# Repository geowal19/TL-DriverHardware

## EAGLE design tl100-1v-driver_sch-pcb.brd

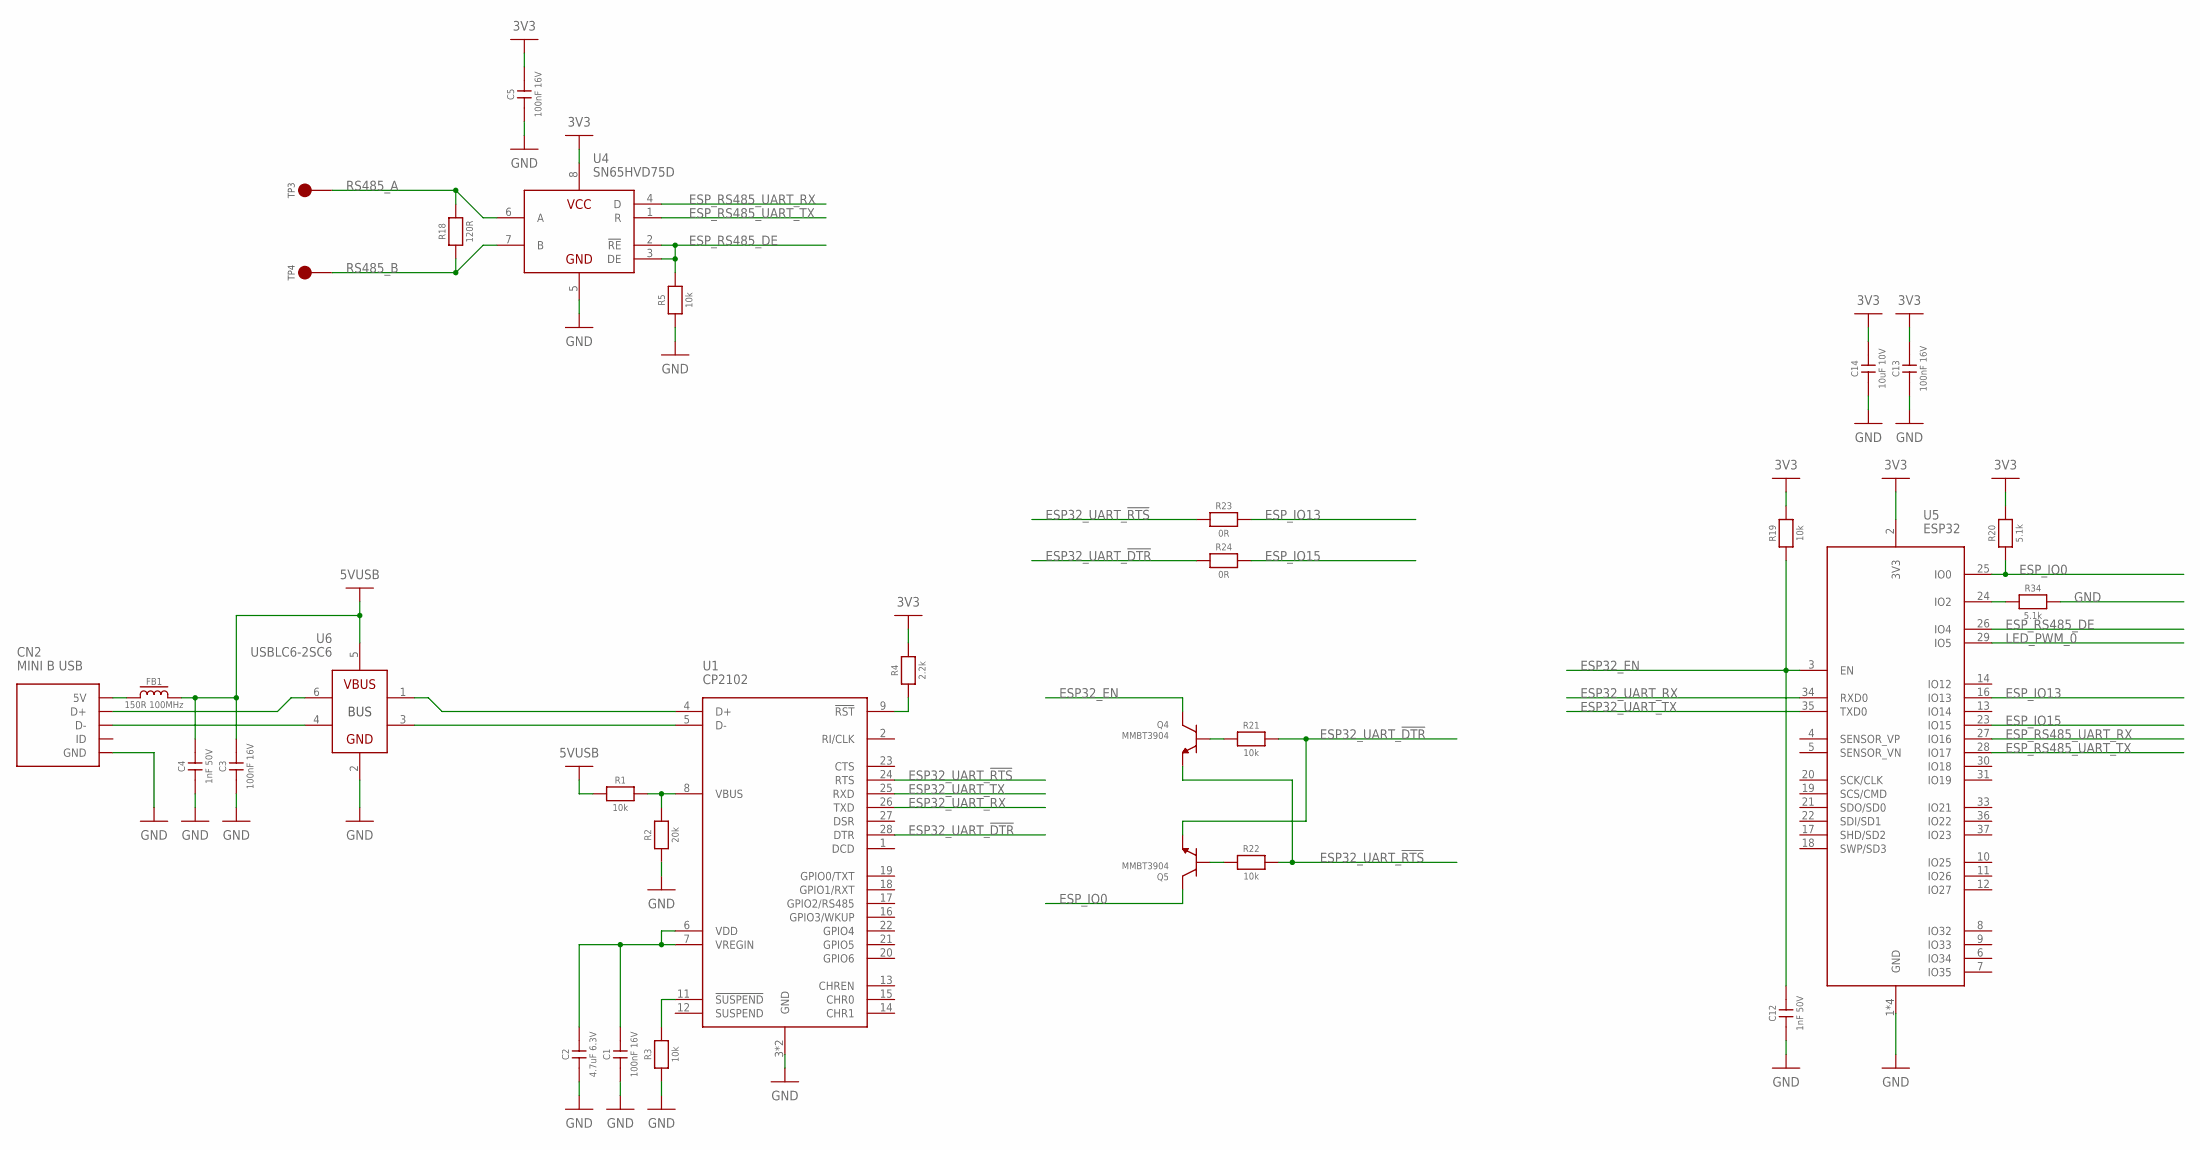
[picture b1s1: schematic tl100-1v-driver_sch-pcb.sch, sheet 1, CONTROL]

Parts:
C1, C3, C5, C13: 100nF 16V; 0603
C2: 4.7uF 6.3V; 0603
C4, C12: 1nF 50V; 0603
C14: 10uF 10V; 0603
CN2: MINI B USB; MUSB-05-S-B-SM-A
FB1: 150R 100MHz; 1206
Q4, Q5: MMBT3904; SOT23-3
R1, R3, R5, R19, R21, R22: 10k; 0603
R2: 20k; 0603
R4: 2.2k; 0603
R18: 120R; 0603
R20, R34: 5.1k; 0603
R23, R24: 0R; 0603
TP3, TP4: 2MM_TEST_POINT; 2MM_TEST_PAD
U1: CP2102; QFN28
U4: SN65HVD75D; SO8
U5: ESP32; ESP32-WROOM-32D
U6: USBLC6-2SC6; SOT23-6

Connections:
3V3: C5.2, C13.2, C14.2, R4.2, R19.2, R20.2, U4.8 (VCC), U5.2 (3V3); also elsewhere on the board
5VUSB: C3.2, C4.2, FB1.2, R1.1, U6.5 (VBUS); also elsewhere on the board
ESP32_EN: C12.2, Q4.2 (C), R19.1, U5.3 (EN)
ESP32_UART_!DTR: Q5.3 (E), R21.2, R24.1, U1.28 (DTR)
ESP32_UART_!RTS: Q4.3 (E), R22.2, R23.1, U1.24 (RTS)
ESP32_UART_RX: U1.26 (TXD), U5.34 (RXD0)
ESP32_UART_TX: U1.25 (RXD), U5.35 (TXD0)
ESP_IO0: Q5.2 (C), R20.1, U5.25 (IO0)
ESP_IO13: R23.2, U5.16 (IO13)
ESP_IO15: R24.2, U5.23 (IO15)
ESP_RS485_DE: R5.2, U4.2 (!RE), U4.3 (DE), U5.26 (IO4)
ESP_RS485_UART_RX: U4.4 (D), U5.27 (IO16)
ESP_RS485_UART_TX: U4.1 (R), U5.28 (IO17)
GND: C1.1, C2.1, C3.1, C4.1, C5.1, C12.1, C13.1, C14.1, CN2.GND, CN2.SHIELD1 (GND), CN2.SHIELD2 (GND), CN2.SHIELD3 (GND), CN2.SHIELD4 (GND), R2.1, R3.1, R5.1, R34.2, U1.3 (GND), U1.29 (GND), U4.5 (GND), U5.1 (GND), U5.15 (GND), U5.38 (GND), U5.39 (GND), U6.2 (GND); also elsewhere on the board
LED_PWM_0: U5.29 (IO5); also elsewhere on the board
unnamed: R1.2, R2.2, U1.8 (VBUS)
unnamed: R4.1, U1.9 (!RST)
unnamed: R3.2, U1.11 (!SUSPEND)
unnamed: C1.2, C2.2, U1.6 (VDD), U1.7 (VREGIN)
unnamed: R34.1, U5.24 (IO2)
unnamed: CN2.VCC (5V), FB1.1
unnamed: CN2.D-, U6.4 (D-OUT)
unnamed: CN2.D+, U6.6 (D+_OUT)
unnamed: U1.5 (D-), U6.3 (D-_IN)
unnamed: U1.4 (D+), U6.1 (D+_IN)
unnamed: Q4.1 (B), R21.1
unnamed: Q5.1 (B), R22.1
RS485_A: R18.2, TP3.1, U4.6 (A)
RS485_B: R18.1, TP4.1, U4.7 (B)

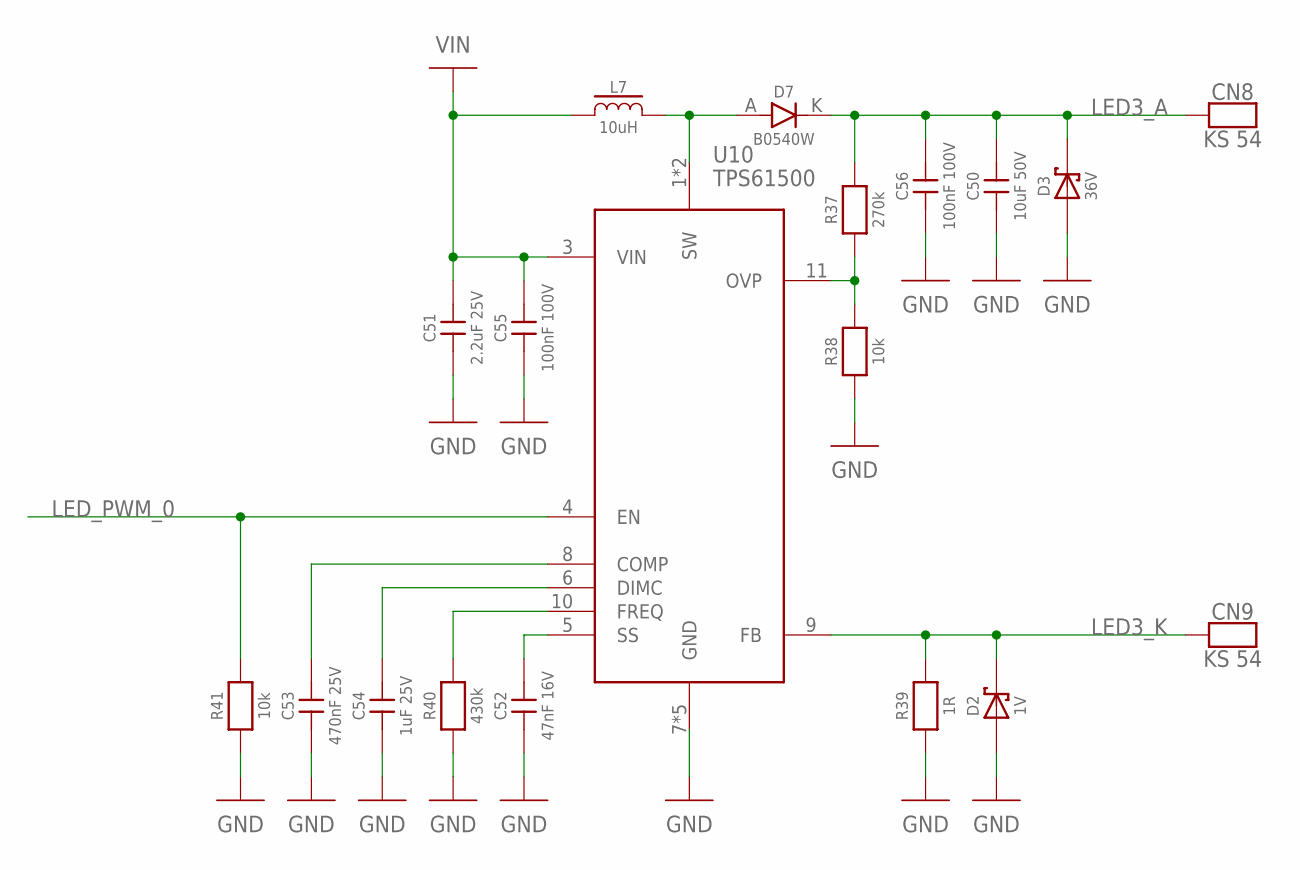
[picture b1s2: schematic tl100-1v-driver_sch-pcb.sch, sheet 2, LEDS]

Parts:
C50: 10uF 50V; 1210
C51: 2.2uF 25V; 0603
C52: 47nF 16V; 0603
C53: 470nF 25V; 0603
C54: 1uF 25V; 0603
C55, C56: 100nF 100V; 0603
CN8, CN9: KS 54; KEYSTONE_54
D2: 1V; SC-79
D3: 36V; SOT23-3
D7: B0540W; SOD-123
L7: 10uH; SRN6045
R37: 270k; 0603
R38, R41: 10k; 0603
R39: 1R; 1206
R40: 430k; 0603
U10: TPS61500; HTSSOP14-4.5

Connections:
GND: C50.1, C51.1, C52.1, C53.1, C54.1, C55.1, C56.1, D2.A, D3.1 (A), R38.1, R39.1, R40.1, R41.1, U10.7 (GND), U10.12 (GND), U10.13 (GND), U10.14 (GND), U10.PAD (GND); also elsewhere on the board
LED3_A: C50.2, C56.2, CN8.P$1, CN8.P$2, CN8.P$3, D3.2 (K), D7.K, R37.2
LED3_K: CN9.P$1, CN9.P$2, CN9.P$3, D2.K, R39.2, U10.9 (FB)
LED_PWM_0: R41.2, U10.4 (EN); also elsewhere on the board
unnamed: C52.2, U10.5 (SS)
unnamed: R40.2, U10.10 (FREQ)
unnamed: C54.2, U10.6 (DIMC)
unnamed: C53.2, U10.8 (COMP)
unnamed: R37.1, R38.2, U10.11 (OVP)
unnamed: D7.A, L7.2, U10.1 (SW), U10.2 (SW)
VIN: C51.2, C55.2, L7.1, U10.3 (VIN); also elsewhere on the board

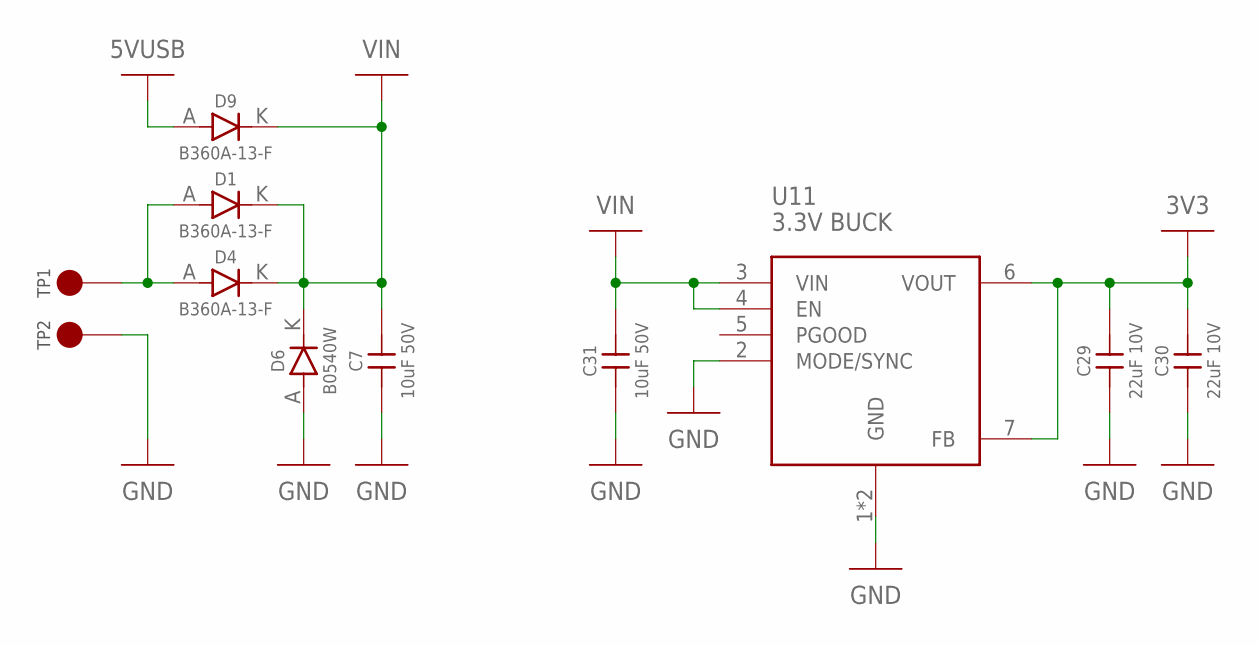
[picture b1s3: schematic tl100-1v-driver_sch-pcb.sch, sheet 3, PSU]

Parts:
C7, C31: 10uF 50V; 1210
C29, C30: 22uF 10V; 1206
D1, D4, D9: B360A-13-F; DO214AC
D6: B0540W; SOD-123
TP1, TP2: 2MM_TEST_POINT; 2MM_TEST_PAD
U11: 3.3V BUCK; TI_MICROSIP_10

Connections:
3V3: C29.2, C30.2, U11.6 (VOUT), U11.7 (FB); also elsewhere on the board
5VUSB: D9.A; also elsewhere on the board
GND: C7.1, C29.1, C30.1, C31.1, D6.A, TP2.1, U11.1 (GND), U11.2 (MODE/SYNC), U11.PAD (GND); also elsewhere on the board
unnamed: D1.A, D4.A, TP1.1
VIN: C7.2, C31.2, D1.K, D4.K, D6.K, D9.K, U11.3 (VIN), U11.4 (EN); also elsewhere on the board

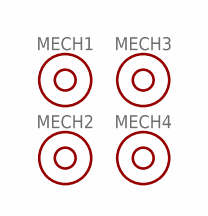
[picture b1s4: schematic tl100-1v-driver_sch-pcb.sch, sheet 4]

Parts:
MECH1, MECH2, MECH3, MECH4: 6mm x 3mm; MOUNTHOLE_6X3

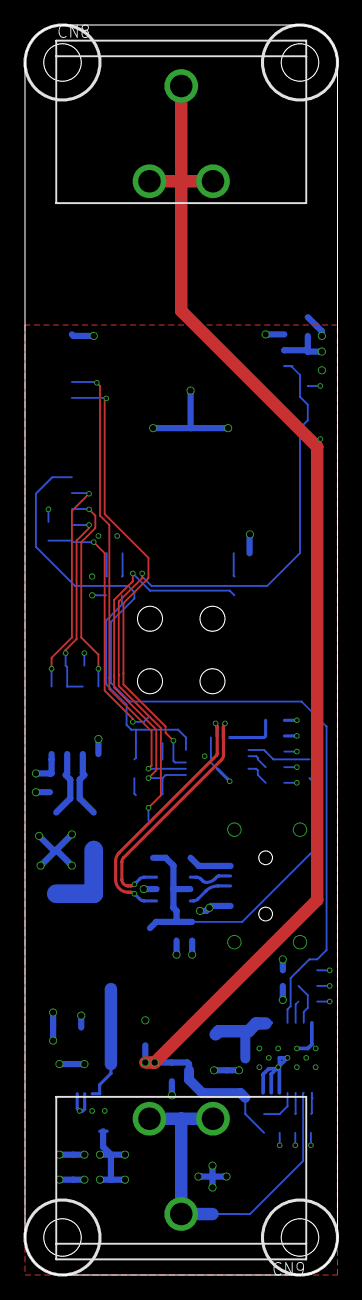
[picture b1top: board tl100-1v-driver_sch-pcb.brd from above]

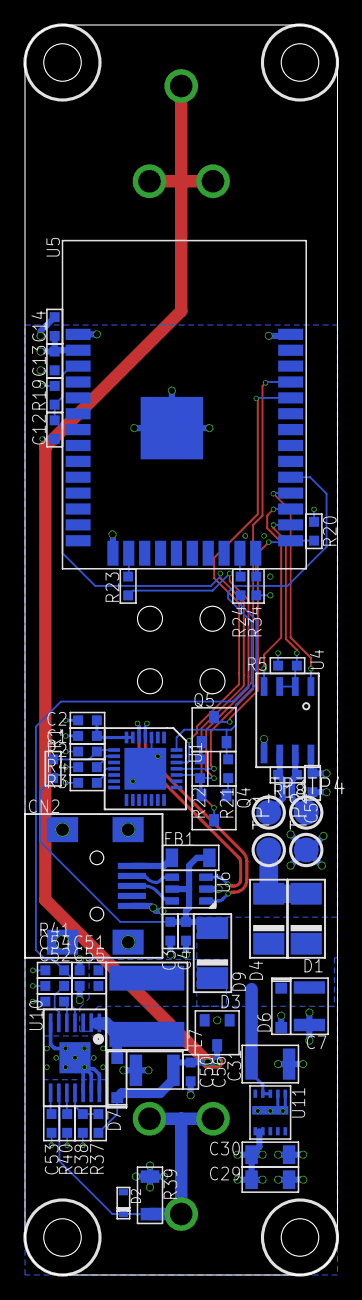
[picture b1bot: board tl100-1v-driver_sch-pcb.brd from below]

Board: 4 copper layers, 25.0 x 100.0 mm, 65 parts (59 on the bottom side), 39 nets.

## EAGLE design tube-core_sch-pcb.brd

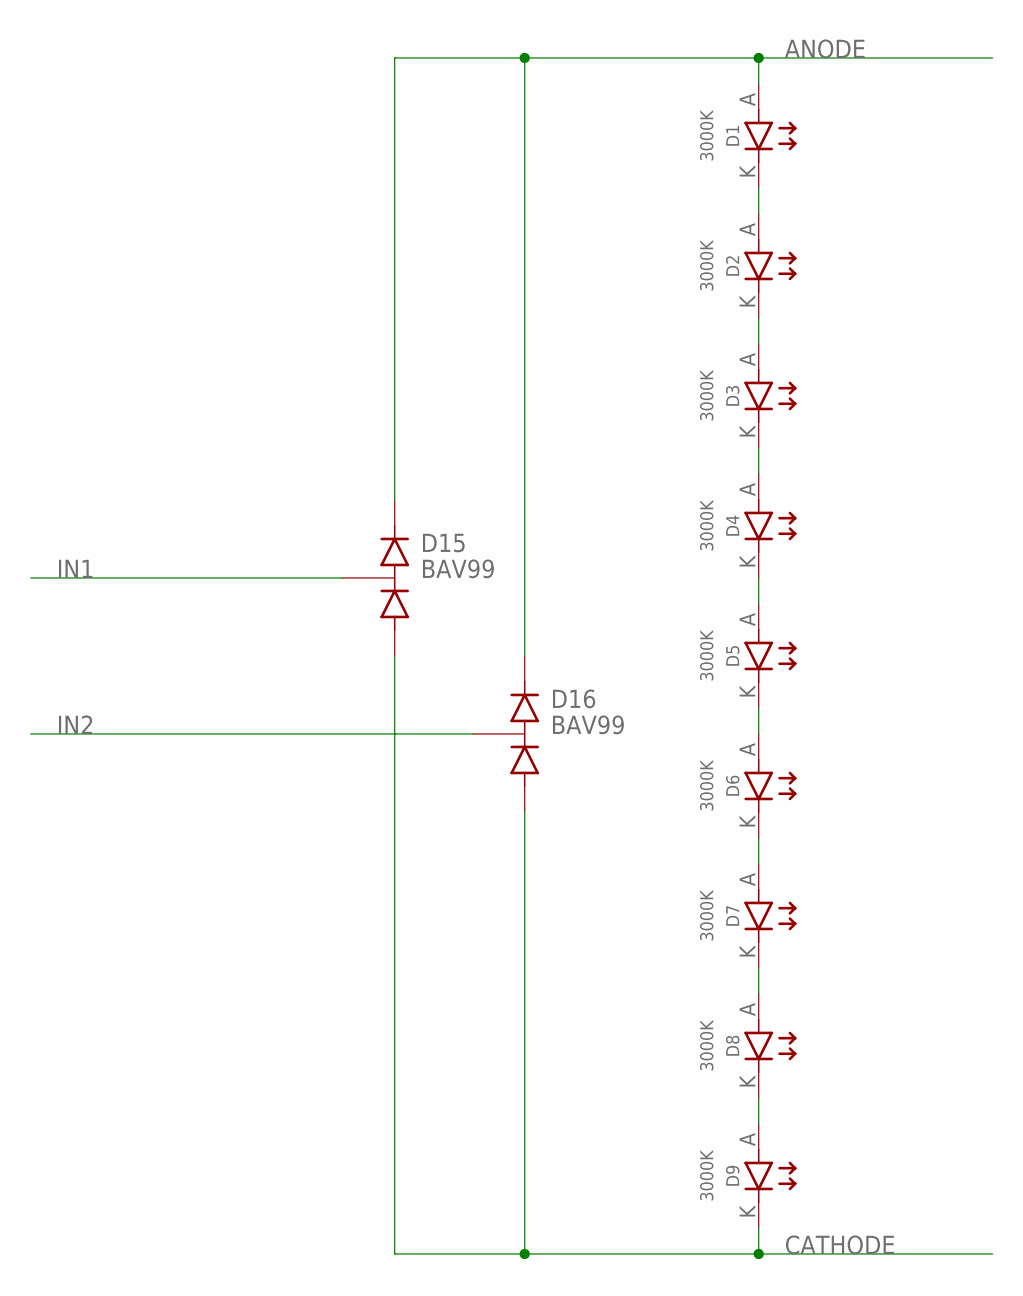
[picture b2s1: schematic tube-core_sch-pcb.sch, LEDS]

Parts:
D1, D2, D3, D4, D5, D6, D7, D8, D9: 3000K; MP-1616
D15, D16: BAV99; SOT23-3

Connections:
ANODE: D1.A, D15.3 (K), D16.3 (K)
CATHODE: D9.K, D15.1 (A), D16.1 (A)
IN1: D15.2 (AK)
IN2: D16.2 (AK)
unnamed: D1.K, D2.A
unnamed: D2.K, D3.A
unnamed: D3.K, D4.A
unnamed: D4.K, D5.A
unnamed: D5.K, D6.A
unnamed: D6.K, D7.A
unnamed: D7.K, D8.A
unnamed: D8.K, D9.A

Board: 2 copper layers, 11 parts (2 on the bottom side), 10 nets, no tracks yet.

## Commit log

2019-10-20 nearly done first rev
2019-10-20 First revision done, need to test ESP32 SPi
2019-10-21 Latest in fusion, need to pull new core design
2019-10-22 Progress
2019-10-22 Recreated core with new diodes
2019-10-22 Driver passes DRC ready to create outputs
2019-10-30 Changing ESP32 and STM32 interface to UART
2019-10-30 ESP and STM UART link established
2019-10-30 Tube core complete
2019-11-07 First revision of the driver complete
2019-11-07 Improved BoM
2019-11-12 New LED design
2019-11-15 Latest from old repo
2019-11-28 Working on rev 2
2019-12-08 Routed and passes DRC
2019-12-08 PWMs routed
2019-12-08 Passes DRC
2019-12-14 tl100-1 done
2019-12-14 tl100-4 done
2019-12-14 tl300-4V done
2019-12-14 All made to work with seal around the edge
